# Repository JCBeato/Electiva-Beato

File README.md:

#  DISEÑO MECATRÓNICO [ELECTIVA]

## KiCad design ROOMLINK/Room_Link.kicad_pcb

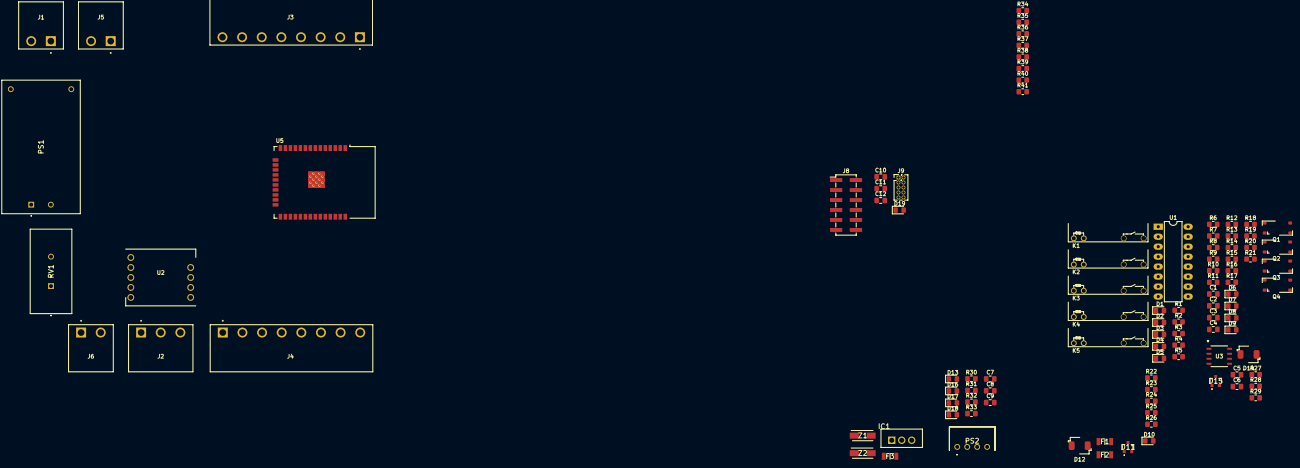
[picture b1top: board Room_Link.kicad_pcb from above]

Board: 2 copper layers, 102 parts (0 on the bottom side), 87 nets, no tracks yet.

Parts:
C1, C2, C3, C4, C10, C12: 0.1uF; C_0805_2012Metric_Pad1.18x1.45mm_HandSolder
C5: 1 uF; C_0805_2012Metric_Pad1.18x1.45mm_HandSolder
C6: 0.1 uF; C_0805_2012Metric_Pad1.18x1.45mm_HandSolder
C7, C8: 0.1uF 25v; C_0805_2012Metric_Pad1.18x1.45mm_HandSolder
C9: 47uF 10; C_0805_2012Metric_Pad1.18x1.45mm_HandSolder
C11: 22 uF; C_0805_2012Metric_Pad1.18x1.45mm_HandSolder
D1, D2, D3, D4, D5, D6, D7, D8, D9, D10, D13, D16, D17, D18, D19: LED; LED_0805_2012Metric_Pad1.15x1.40mm_HandSolder
D11, D15: SM712-02HTG; SM71202HTG
D12, D14: SMBJ12CA
F1, F2, F3: PTS120660V010; FUSC3216X68N
IC1: LM1117T-3.3; TO254P470X1016X2222-3P
J1, J5, J6: TBP04R12-500-02BE; CUI_TBP04R12-500-02BE
J2: TBP04R12-500-03BE; CUI_TBP04R12-500-03BE
J3, J4: TBP04R12-500-08BE; CUI_TBP04R12-500-08BE
J8: Screw_Terminal_01x06; PinHeader_2x06_P2.54mm_Vertical_SMD
J9: Conn_ARM_JTAG_SWD_10; PinHeader_2x05_P1.27mm_Vertical
K1, K2, K3, K4, K5: ADW11; AZ921
PS1: HLK-PM12; HLKPM12
PS2: B0505S-W2R2; B0505SW2R2
Q1, Q2, Q3, Q4: FODM2705
R1: 2.4K; R_0805_2012Metric_Pad1.20x1.40mm_HandSolder
R2, R3, R4, R5: 1K; R_0805_2012Metric_Pad1.20x1.40mm_HandSolder
R6, R12, R16, R20: 10k; R_0805_2012Metric_Pad1.20x1.40mm_HandSolder
R7, R8, R14, R18: 330; R_0805_2012Metric_Pad1.20x1.40mm_HandSolder
R9, R10, R15, R19, R25, R26, R27, R29: 10; R_0805_2012Metric_Pad1.20x1.40mm_HandSolder
R11, R13, R17, R21, R32, R41: 470; R_0805_2012Metric_Pad1.20x1.40mm_HandSolder
R22, R23, R24, R31: 2.2k; R_0805_2012Metric_Pad1.20x1.40mm_HandSolder
R28: 10 1%; R_0805_2012Metric_Pad1.20x1.40mm_HandSolder
R30: R; R_0805_2012Metric_Pad1.20x1.40mm_HandSolder
R33, R35: 1k; R_0805_2012Metric_Pad1.20x1.40mm_HandSolder
R34: 22k; R_0805_2012Metric_Pad1.20x1.40mm_HandSolder
R36, R37, R38, R39, R40: 100k; R_0805_2012Metric_Pad1.20x1.40mm_HandSolder
RV1: MOVTP20V275N
U1: ULN2003A; DIP-16_W7.62mm_LongPads
U2: TD521D485H-E
U3: SP485ECN-L; NSOIC-8-L
U5: ESP32-WROOM-32
Z1, Z2: 1SMA5918BT3G; DIOM5226X220N

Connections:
+3.3V: C8.1, C9.1, IC1.2 (OUT), PS2.2 (VIN), R32.1, Z1.2 (A)
+5V: C5.1, C6.1, R6.1, R11.1, R12.1, R13.1, R16.1, R17.1, R20.1, R21.1, U2.2 (GND), U3.8 (VCC)
+12V: C7.1, IC1.3 (IN), K1.1, K2.1, K3.1, K4.1, K5.1, R1.2, R2.2, R3.2, R4.2, R5.2, R31.1
/Room-Link/CON-A-: F2.2, J2.2
/Room-Link/CON-B+: F1.2, J2.3
/Room-Link/CON-DC+: J5.1, R33.1
/Room-Link/CON-FAN1: J3.7, K2.3
/Room-Link/CON-FAN2: J3.6, K3.3
/Room-Link/CON-FAN3: J3.5, K4.3
/Room-Link/CON-IN1+: J4.8, Q1.2 (CATHODE)
/Room-Link/CON-IN1-: J4.7, R10.2
/Room-Link/CON-IN2+: J4.6, R9.2
/Room-Link/CON-IN2-: J4.5, Q2.2 (CATHODE)
/Room-Link/CON-IN3+: J4.4, Q3.2 (CATHODE)
/Room-Link/CON-IN3-: J4.3, R15.2
/Room-Link/CON-IN4+: J4.2, Q4.2 (CATHODE)
/Room-Link/CON-IN4-: J4.1, R19.2
/Room-Link/CON-L1: F3.1, J6.1
/Room-Link/CON-LCDA: J1.1, R29.2
/Room-Link/CON-LCDB+: J1.2, R27.2
/Room-Link/CON-NEUT: J6.2, PS1.1 (AC_1), RV1.2
/Room-Link/CON-OUT1A: J3.3, K5.3
/Room-Link/CON-OUT2A: J3.1, K1.3
/Room-Link/CONTROL/COM_RS485_LCD: R28.1, U5.6 (IO34)
/Room-Link/CONTROL/CON_RS485_eXT: U2.5 (CON), U5.7 (IO35)
/Room-Link/CONTROL/INPUT_1MICRO: C1.1, D6.1 (K), Q1.4 (COLLECTOR), R6.2, U5.25 (IO0)
/Room-Link/CONTROL/INPUT_2MICRO: C2.1, D7.1 (K), Q2.4 (COLLECTOR), R12.2, U5.29 (IO5)
/Room-Link/CONTROL/INPUT_3MICRO: C3.1, D8.1 (K), Q3.4 (COLLECTOR), R16.2, U5.26 (IO4)
/Room-Link/CONTROL/INPUT_4MICRO: C4.1, D9.1 (K), Q4.4 (COLLECTOR), R20.2, U5.24 (IO2)
/Room-Link/CONTROL/RLY_FAN1_MICRO: U1.5 (I5), U5.10 (IO25)
/Room-Link/CONTROL/RLY_FAN2_MICRO: U1.4 (I4), U5.11 (IO26)
/Room-Link/CONTROL/RLY_FAN3_MICRO: U1.3 (I3), U5.12 (IO27)
/Room-Link/CONTROL/RLY_OUT1_MICRO: U1.1 (I1), U5.36 (IO22)
/Room-Link/CONTROL/RLY_OUT2_MICRO: U1.2 (I2), U5.37 (IO23)
/Room-Link/CONTROL/Rx_RS485_eXT: U2.4 (RXD), U5.34 (RXD0/IO3)
/Room-Link/CONTROL/Rx_RS485_lcd: U3.4 (DI), U5.27 (IO16)
/Room-Link/CONTROL/Tx_RS485_LCD: U3.1 (RO), U5.28 (IO17)
/Room-Link/CONTROL/Tx_RS485_eXT: U2.3 (TXD), U5.35 (TXD0/IO1)
/Room-Link/RGND: D11.3, J2.1
EN: C10.2, J9.10 (~RESET), R34.2, R40.2, U5.3 (EN)
Earth: D13.1 (K), PS2.3 (0V), R9.1, R10.1, R15.1, R19.1, Z2.1 (K)
GND: C1.2, C2.2, C3.2, C4.2, C5.2, C6.2, C7.2, C8.2, C9.2, C11.2, C12.2, D15.3, D16.1 (K), D17.1 (K), D18.1 (K), IC1.1 (ADJ/GND), J5.2, J8.5, J9.3 (GND), J9.5 (GND), J9.9 (GNDDetect), PS1.3 (-V0), PS1.4 (+V0), PS2.1 (GND), Q1.3 (EMITTER), Q2.3 (EMITTER), Q3.3 (EMITTER), Q4.3 (EMITTER), U1.8 (GND), U2.1 (VCC), U3.5 (GND), U5.1 (GND), U5.15 (GND), U5.38 (GND), U5.39 (GND), Z1.1 (K)
MTCLK: J9.4 (SWDCLK/TCK), R37.2, U5.16 (IO13)
MTD0: J9.6 (SWO/TDO), R38.2, U5.23 (IO15)
MTD1: J9.8 (NC/TDI), R39.2, U5.14 (IO12)
MTMS: J9.2 (SWDIO/TMS), R36.2
unnamed: D1.2 (A), R1.1
unnamed: D1.1 (K), U1.15 (O2)
unnamed: D2.2 (A), R2.1
unnamed: D2.1 (K), U1.14 (O3)
unnamed: D3.2 (A), R3.1
unnamed: D3.1 (K), U1.13 (O4)
unnamed: D4.2 (A), R4.1
unnamed: D4.1 (K), U1.12 (O5)
unnamed: D5.2 (A), R5.1
unnamed: D5.1 (K), U1.16 (O1)
unnamed: D6.2 (A), R11.2
unnamed: D7.2 (A), R13.2
unnamed: D8.2 (A), R17.2
unnamed: D9.2 (A), R21.2
unnamed: D10.2 (A), R22.2
unnamed: D10.1 (K), D11.2, D12.1, R23.2, R26.1, U2.9 (A)
unnamed: D13.2 (A), R30.2
unnamed: D16.2 (A), R31.2
unnamed: D17.2 (A), R32.2
unnamed: D18.2 (A), R33.2
unnamed: D19.2 (A), R41.1
unnamed: D19.1 (K), U5.9 (IO33)
unnamed: F1.1, R25.2
unnamed: F2.1, R26.2
unnamed: J8.2, U5.30 (IO18)
unnamed: J8.3, U5.8 (IO32)
unnamed: J8.4, U5.31 (IO19)
unnamed: J8.6, U5.33 (IO21)
unnamed: J9.1 (VTref), R35.2
unnamed: F3.2, PS1.2 (AC_2), RV1.1
unnamed: Q1.1 (ANODE), R7.2
unnamed: Q2.1 (ANODE), R8.2
unnamed: Q3.1 (ANODE), R14.2
unnamed: Q4.1 (ANODE), R18.2
unnamed: D11.1, D12.2, R24.2, R25.1, U2.8 (B)
unnamed: R24.1, U2.10 (RGND)
unnamed: R22.1, R23.1, U2.7 (VO)
unnamed: R28.2, U3.2 (*RE), U3.3 (DE)
unnamed: D14.2, D15.1, R29.1, U3.6 (A)
unnamed: D14.1, D15.2, R27.1, U3.7 (B)
VDD: C10.1, C11.1, C12.1, J8.1, PS2.4 (+VO), R7.1, R8.1, R14.1, R18.1, R30.1, R34.1, R35.1, R36.1, R37.1, R38.1, R39.1, R40.1, R41.2, U5.2 (VDD), Z2.2 (A)

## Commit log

2023-06-17 Rename Electiva tarea 1.txt to Prueba.txt
